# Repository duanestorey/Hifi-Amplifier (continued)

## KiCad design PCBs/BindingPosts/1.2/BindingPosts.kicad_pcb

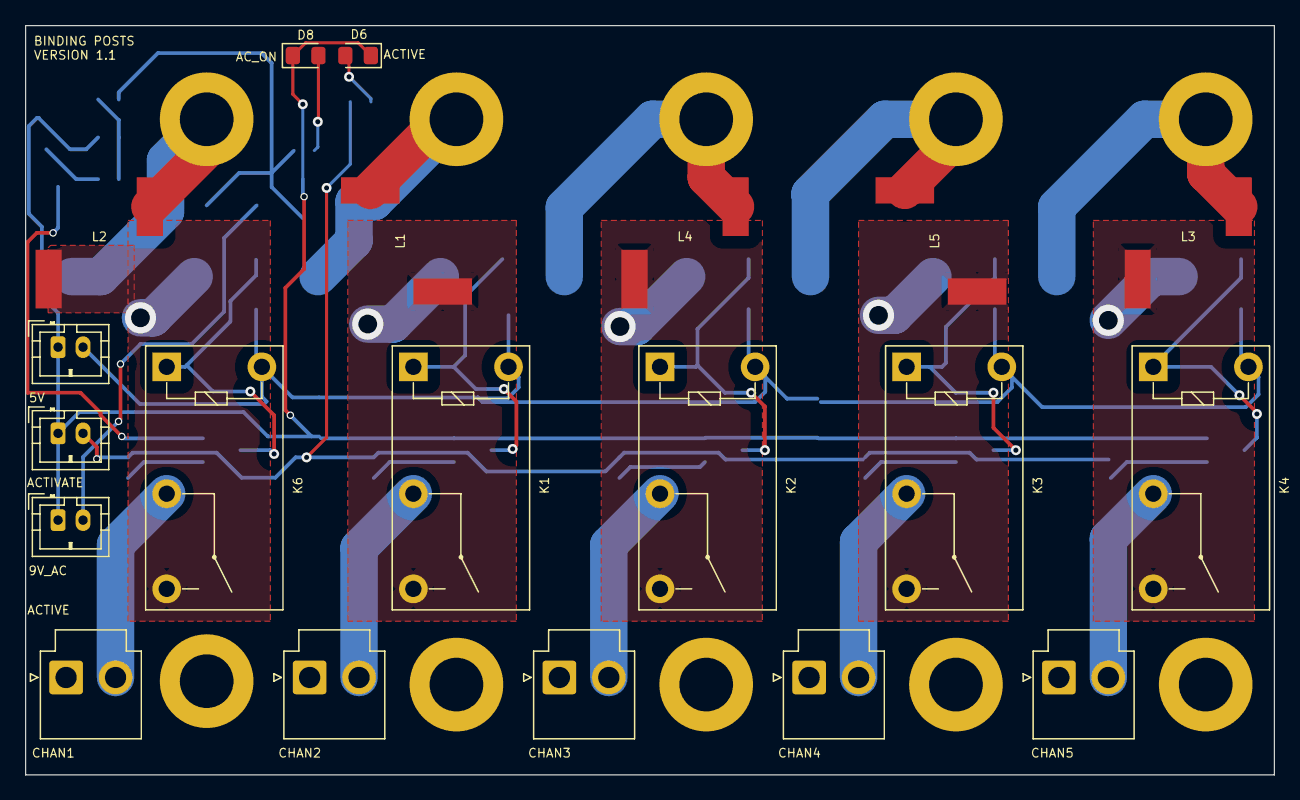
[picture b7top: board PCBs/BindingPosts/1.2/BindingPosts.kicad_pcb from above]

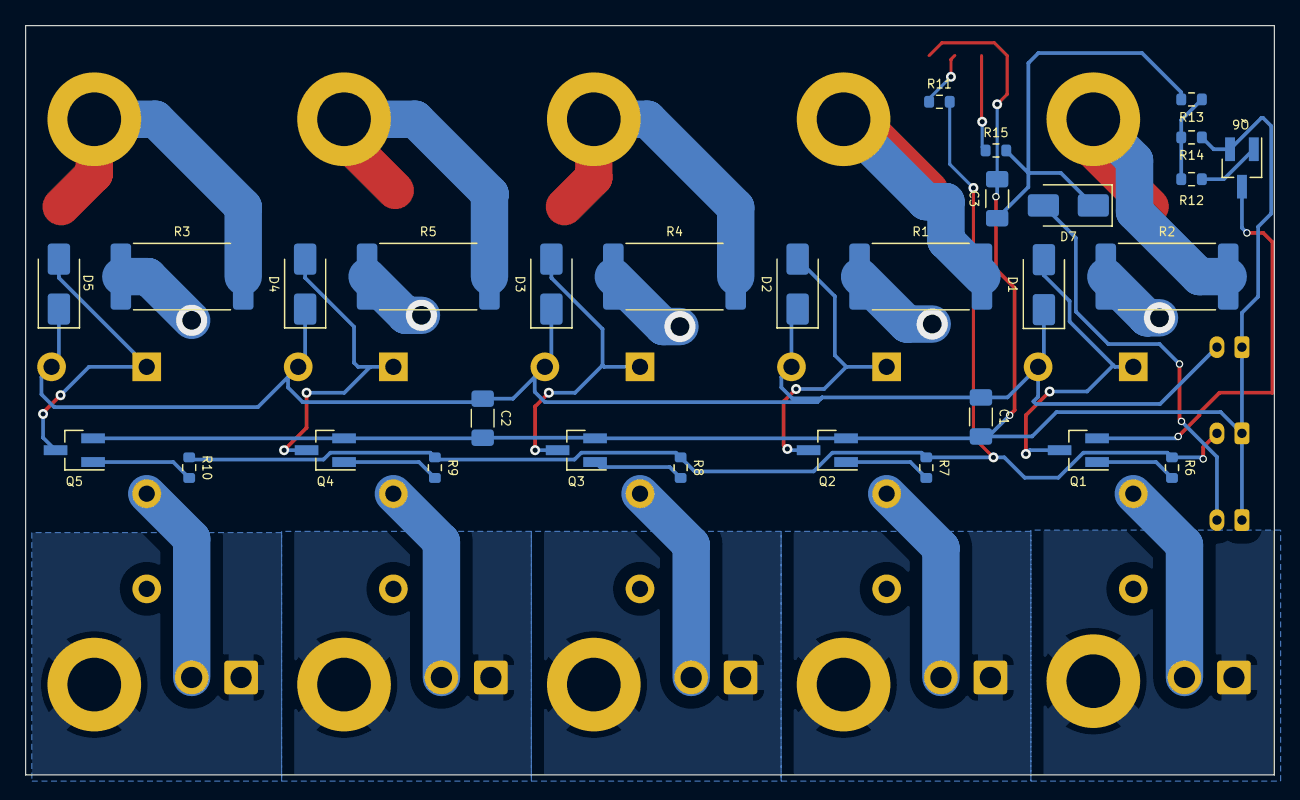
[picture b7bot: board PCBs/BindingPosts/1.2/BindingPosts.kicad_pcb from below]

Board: 2 copper layers, 100.0 x 60.0 mm, 60 parts (30 on the bottom side), 40 nets.

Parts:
C1, C2: 10U; C_1206_3216Metric_Pad1.33x1.80mm_HandSolder
C3: 1U; C_1206_3216Metric_Pad1.33x1.80mm_HandSolder
D1, D2, D3, D4, D5, D7: 1N4001; D_SMA
D6: RED; LED_0805_2012Metric_Pad1.15x1.40mm_HandSolder
D8: YELLOW; LED_0805_2012Metric_Pad1.15x1.40mm_HandSolder
H1, H2, H3, H4, H5, H6, H7, H8, H9, H10: MountingHole_Pad; MountingHole_4.3mm_M4_DIN965_Pad
J1, J2, J3, J4, J5: Conn_01x02_Male; JST_VH_B2P-VH-B_1x02_P3.96mm_Vertical
J6, J7, J8: Conn_01x02_Pin; JST_PH_B2B-PH-K_1x02_P2.00mm_Vertical
K1, K2, K3, K4, K6: G5Q-1; Relay_SPST_Omron-G5Q-1A
L1, L2, L4, L5: 0.5u; Abracon 4125C Air Core Inductor 538nH
L3: 538n; Abracon 4125C Air Core Inductor 538nH
Q1, Q2, Q3, Q4, Q5, Q6: 2SC1945; SOT-23_Handsoldering
R1, R2, R4, R5: 6.8R; R_4020_10251Metric_Pad1.65x5.30mm_HandSolder
R3: 7.5R; R_4020_10251Metric_Pad1.65x5.30mm_HandSolder
R6, R7, R8, R9, R10, R12: 1K; R_0603_1608Metric
R11: 360R; R_0603_1608Metric
R13: 30K; R_0603_1608Metric
R14: 10K; R_0603_1608Metric
R15: 3300R; R_0603_1608Metric

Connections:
5V: C1.1, C2.1, D1.1 (K), D2.1 (K), D3.1 (K), D4.1 (K), D5.1 (K), J6.2, K1.5, K2.5, K3.5, K4.5, K6.5
9VAC: D7.2 (A), J8.2
12V: C3.1, D7.1 (K), R13.2, R15.2
ACTIVATE: J7.2, R6.1, R7.1, R8.1, R9.1, R10.1, R11.2
AC_ACTIVE: R12.1, R13.1, R14.2
GND: C1.2, C2.2, C3.2, D6.1 (K), D8.1 (K), J6.1, J7.1, J8.1, Q2.2 (E), Q3.2 (E), Q4.2 (E), Q5.2 (E), Q6.2 (E), R14.1
unnamed: D1.2 (A), K6.1, Q1.3 (C)
unnamed: D2.2 (A), K1.1, Q2.3 (C)
unnamed: D3.2 (A), K2.1, Q3.3 (C)
unnamed: D4.2 (A), K3.1, Q4.3 (C)
unnamed: D5.2 (A), K4.1, Q5.3 (C)
unnamed: D6.2 (A), R11.1
unnamed: D8.2 (A), R15.1
unnamed: Q1.1 (B), R6.2
unnamed: Q1.2 (E), Q6.3 (C)
unnamed: Q2.1 (B), R7.2
unnamed: Q3.1 (B), R8.2
unnamed: Q4.1 (B), R9.2
unnamed: Q5.1 (B), R10.2
unnamed: Q6.1 (B), R12.2
PGND: H4.1, J2.1
PGND2: H3.1, J1.1
PGND3: H8.1, J4.1
PGND4: H10.1, J5.1
PGND5: H7.1, J3.1
SIGNAL1: J2.2, K6.2
SIGNAL1_OUT: K6.3, L2.2, R2.1
SIGNAL2: J1.2, K1.2
SIGNAL2_OUT: K1.3, L1.2, R1.1
SIGNAL3: J4.2, K2.2
SIGNAL3_OUT: K2.3, L4.2, R4.1
SIGNAL4: J5.2, K3.2
SIGNAL4_OUT: K3.3, L5.2, R5.1
SIGNAL5: J3.2, K4.2
SIGNAL5_OUT: K4.3, L3.2, R3.1
SPEAKER: H2.1, L2.1, R2.2
SPEAKER2: H1.1, L1.1, R1.2
SPEAKER3: H6.1, L4.1, R4.2
SPEAKER4: H9.1, L5.1, R5.2
SPEAKER5: H5.1, L3.1, R3.2
